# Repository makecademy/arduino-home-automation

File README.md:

arduino-home-automation
=======================

Code for the Arduino Home Automation book published by PacktPub

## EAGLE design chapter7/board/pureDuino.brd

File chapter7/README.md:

chapter7
==================

Code for the seventh chapter of the book, dedicated to building your own home automation systems
- low_power: an example low-power sketch for Arduino
- board: the EAGLE design files for the example design of this chapter
- case: the OpenSCAD & STL files for the case of the example design

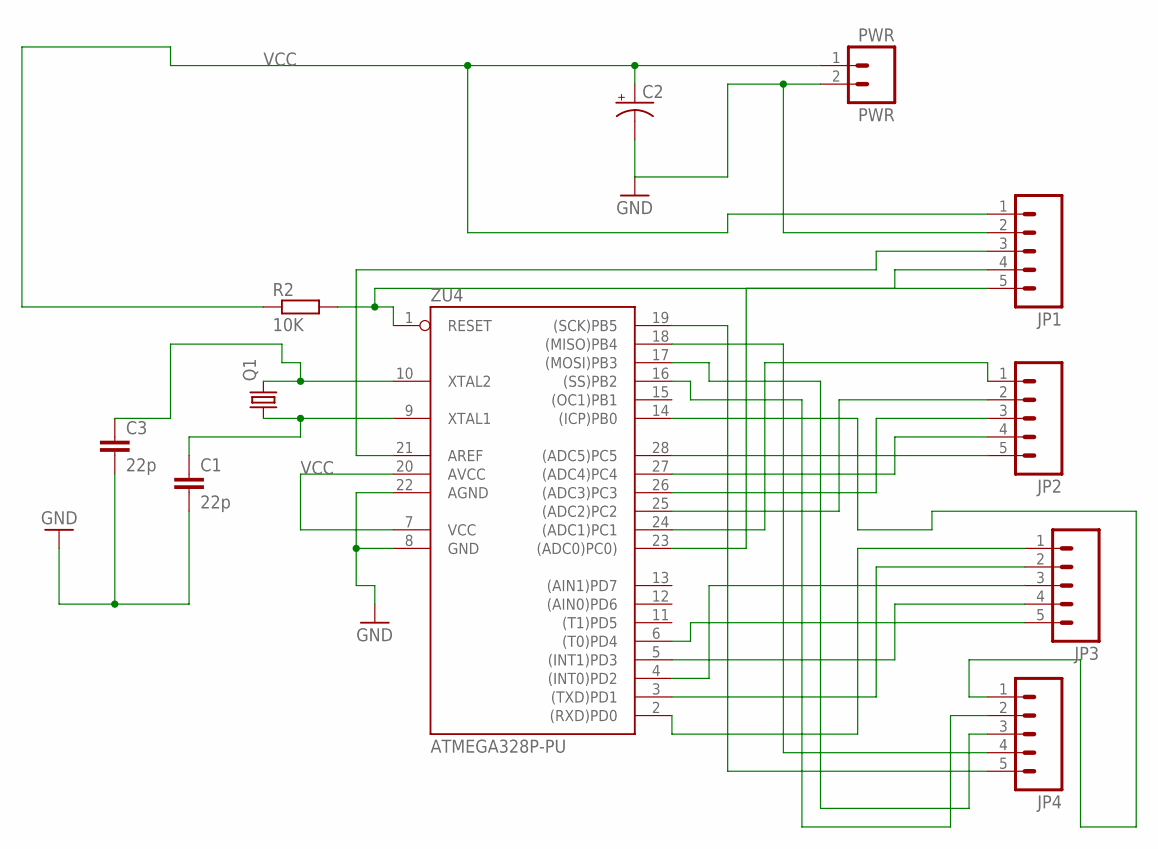
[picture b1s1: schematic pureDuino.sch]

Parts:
C1, C3: 22p; C050-025X075
C2: CAP_POLPTH1; CPOL-RADIAL-100UF-25V
JP1, JP2, JP3, JP4: M05PTH; 1X05
PWR: PWR; 1X02
Q1: CRYSTALHC49S; HC49/S
R2: 10K; 0207/7
ZU4: ATMEGA328P-PU; DIL28-3

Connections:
GND: C1.2, C2.2 (-), C3.2, JP1.2, PWR.2, ZU4.8 (GND), ZU4.22 (AGND)
unnamed: JP1.3, ZU4.21 (AREF)
unnamed: JP1.5, ZU4.23 ((ADC0)PC0))
unnamed: JP1.4, R2.2, ZU4.1 (RESET)
unnamed: C1.1, Q1.1, ZU4.9 (XTAL1)
unnamed: JP2.1, ZU4.24 ((ADC1)PC1)
unnamed: JP2.2, ZU4.25 ((ADC2)PC2)
unnamed: JP2.3, ZU4.26 ((ADC3)PC3)
unnamed: JP2.4, ZU4.27 ((ADC4)PC4)
unnamed: JP2.5, ZU4.28 ((ADC5)PC5)
unnamed: JP4.5, ZU4.19 ((SCK)PB5)
unnamed: JP3.1, ZU4.2 ((RXD)PD0)
unnamed: JP3.2, ZU4.3 ((TXD)PD1)
unnamed: JP3.3, ZU4.4 ((INT0)PD2)
unnamed: JP3.4, ZU4.5 ((INT1)PD3)
unnamed: JP3.5, ZU4.6 ((T0)PD4)
unnamed: JP4.4, ZU4.18 ((MISO)PB4)
unnamed: JP4.3, ZU4.17 ((MOSI)PB3)
unnamed: JP4.2, ZU4.16 ((SS)PB2)
unnamed: JP4.1, ZU4.14 ((ICP)PB0)
VCC: C2.1 (+), JP1.1, PWR.1, R2.1, ZU4.7 (VCC), ZU4.20 (AVCC)
XTAL2: C3.1, Q1.2, ZU4.10 (XTAL2)

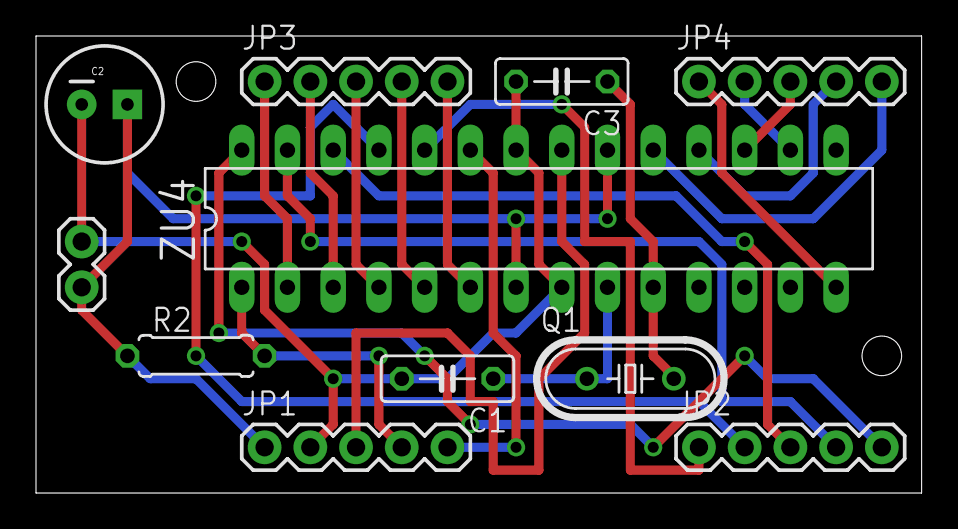
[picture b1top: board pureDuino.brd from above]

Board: 2 copper layers, 49.2 x 25.4 mm, 11 parts (0 on the bottom side), 22 nets.

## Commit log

2014-04-22 second chapter added
2014-04-24 added chapter 1
2014-05-03 added chapter 3
2014-05-07 chapter 4 added
2014-05-07 fix in Xively code
2014-05-08 added chapter5
2014-05-12 added chapter 5
2014-05-12 added chapter 7
2014-05-31 add Ethernet header in motion_sensor.ino
2014-05-31 add Ethernet header in relay_wifi.ino
2014-05-31 connect by domain instead of fixed ip
2014-05-31 connect by domain instead of by ip
    The IP address could change sometime in the future, better be safe and connect through the domain.
    The code is *UNTESTED*!! Please, test it works correctly before merging.
2014-06-03 reverted Xively code to fixed IP
2014-06-04 small fixes

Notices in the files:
parts and their libraries:
SparkFun-Connectors: Licensing: CC v3.0 Share-Alike You are welcome to use this library for commercial purposes.
